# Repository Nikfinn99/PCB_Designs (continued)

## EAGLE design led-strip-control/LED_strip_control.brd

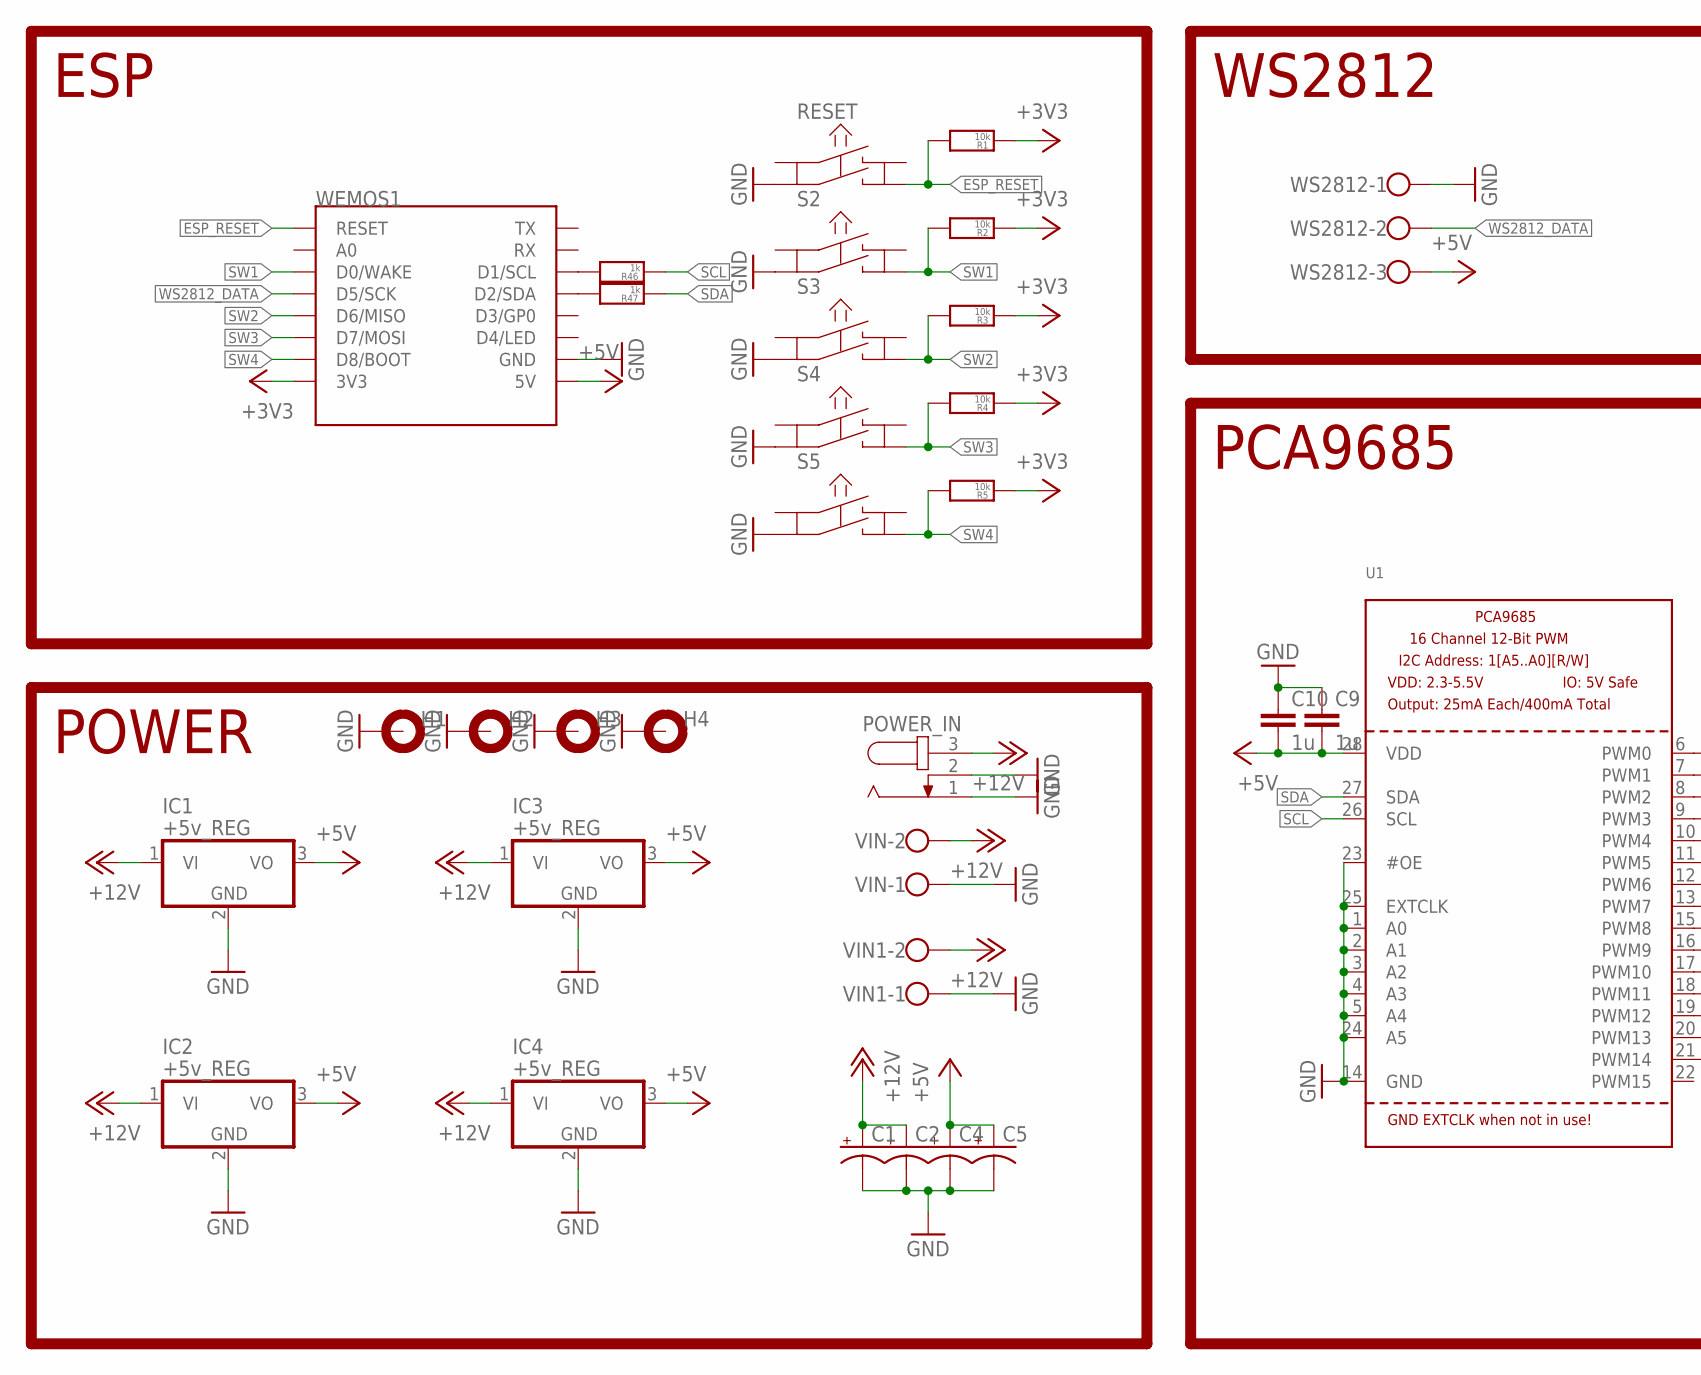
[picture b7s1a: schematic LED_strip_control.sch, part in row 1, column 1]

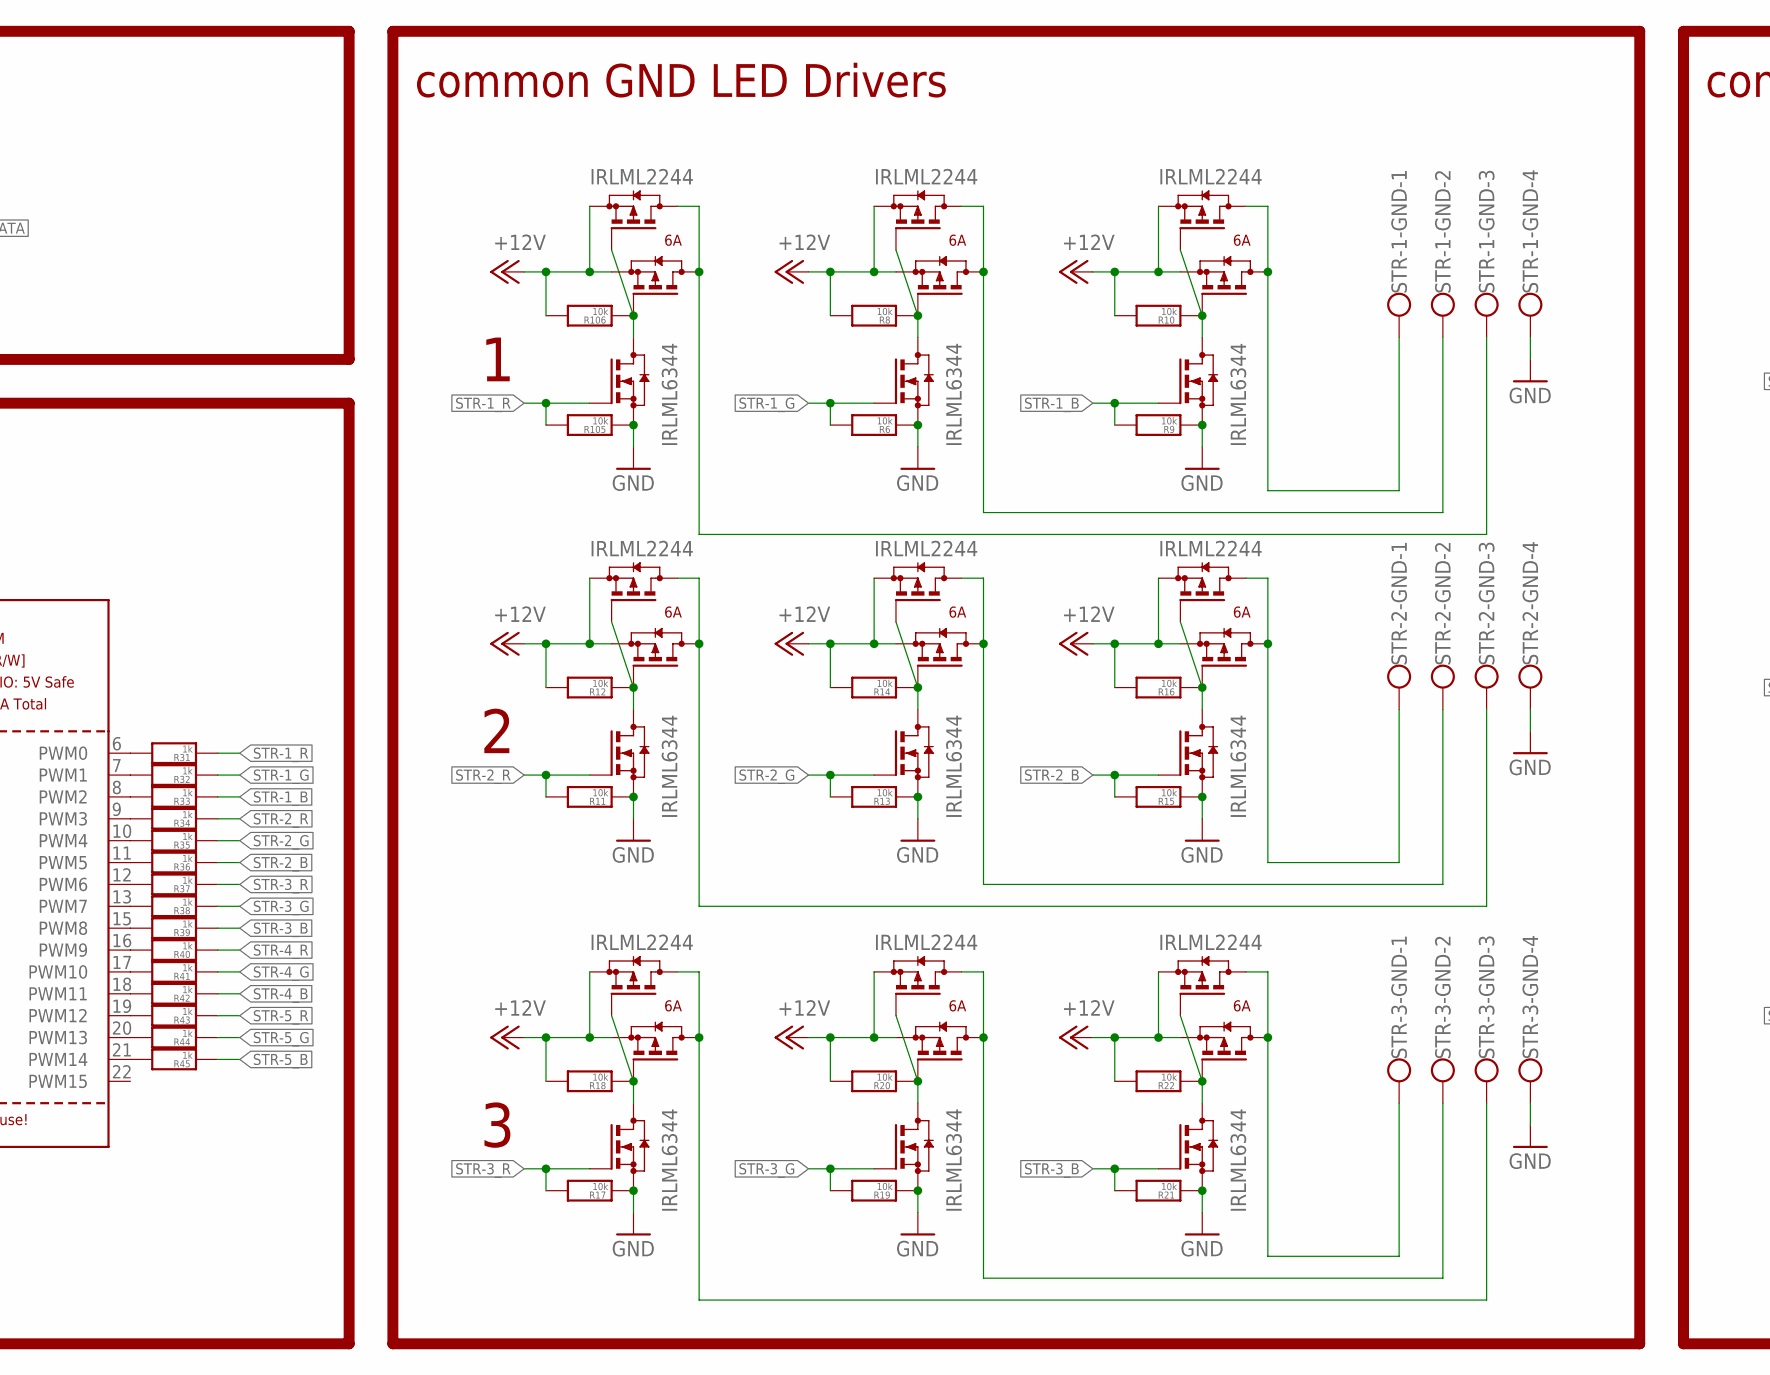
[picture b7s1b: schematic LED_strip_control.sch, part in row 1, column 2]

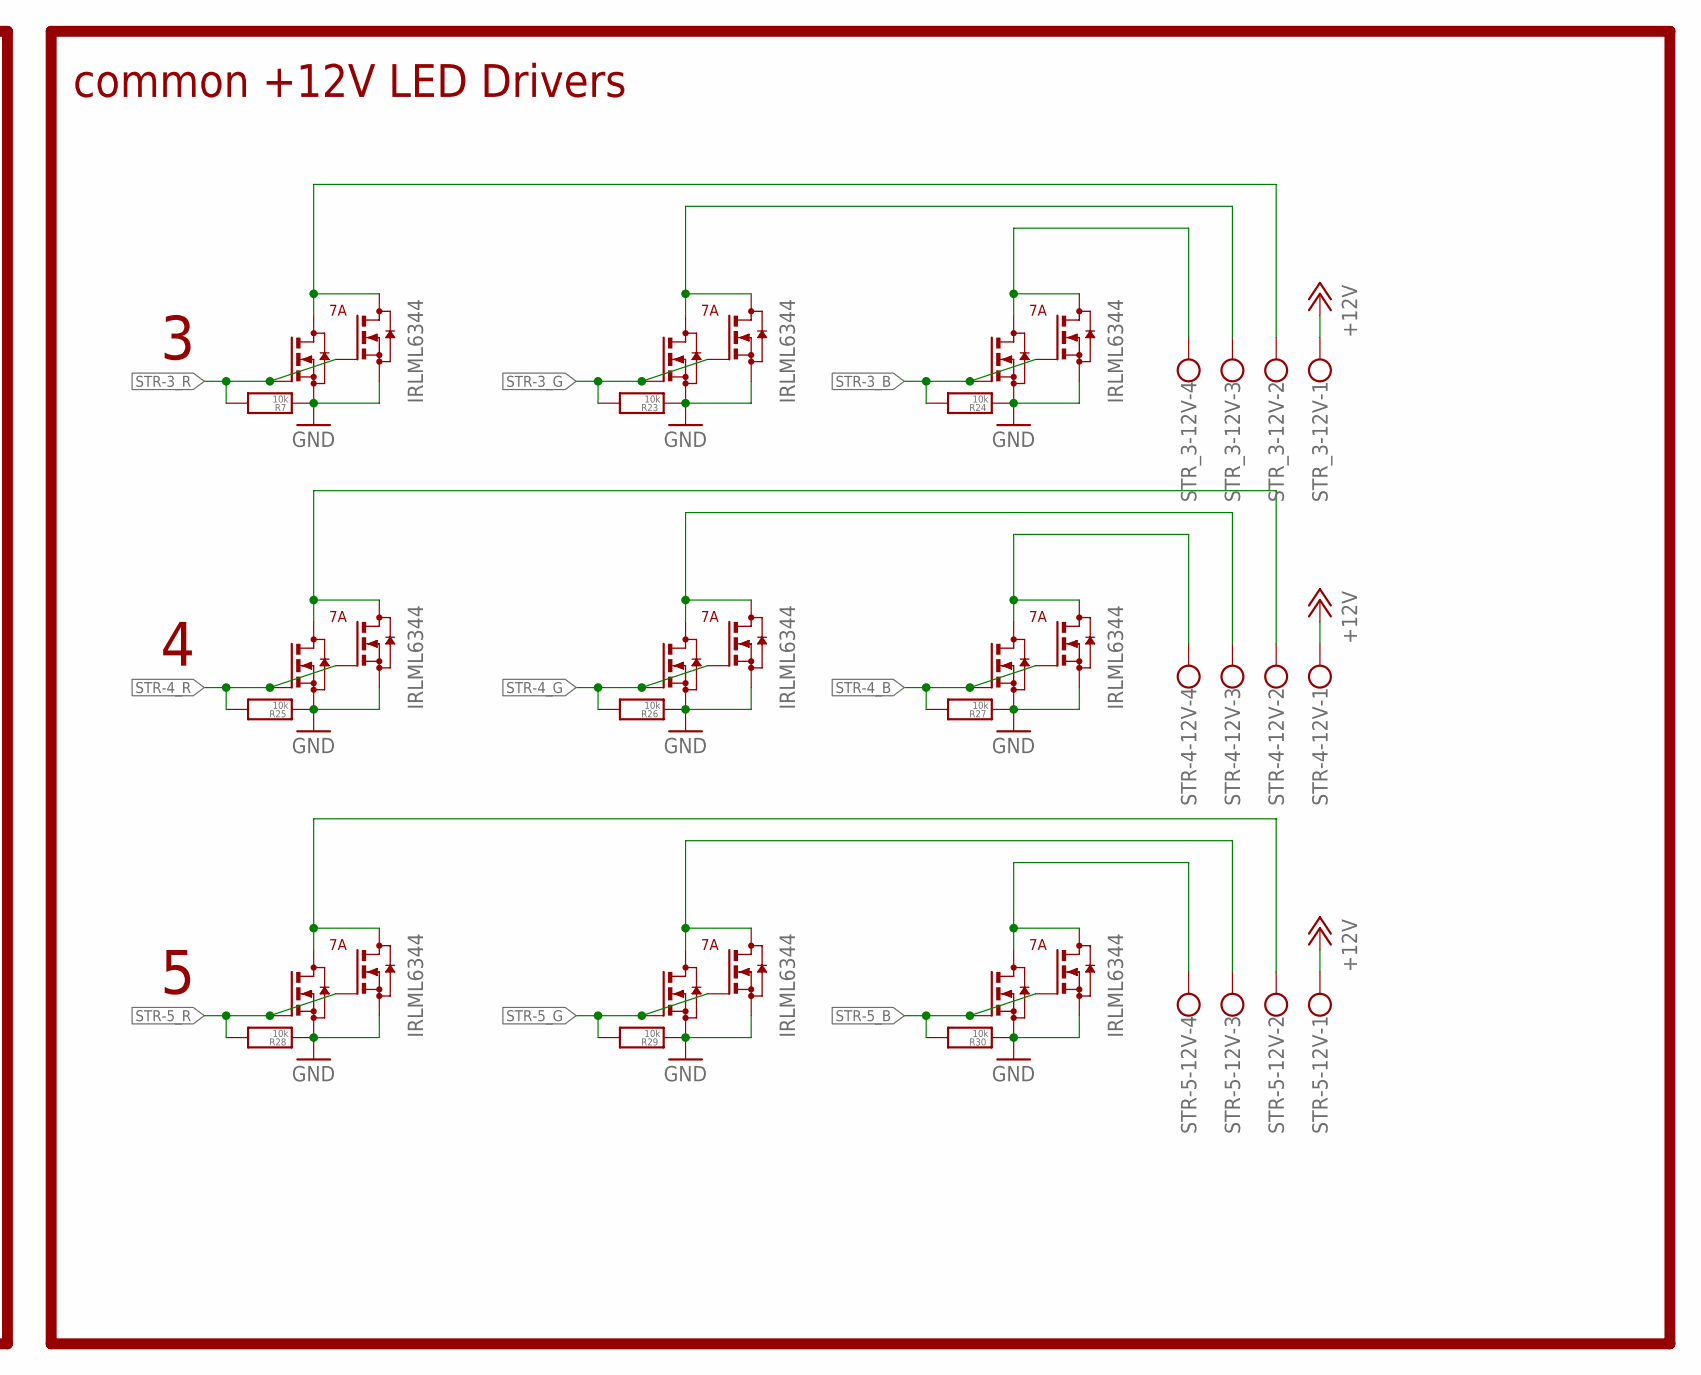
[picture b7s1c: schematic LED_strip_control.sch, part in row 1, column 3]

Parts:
C1, C2, C4, C5: CPOL-USE5-10.5; E5-10,5@1
C9, C10: 1u; C0805
H1, H2, H3, H4: MOUNT-PAD-ROUND3.2; 3,2-PAD
IC1, IC2, IC3, IC4: +5v_REG; TO220V
POWER_IN: RAPC7120; RAPC712
Q1, Q2, Q7, Q8, Q10, Q11, Q13, Q14, Q16, Q17, Q19, Q20, Q22, Q23, Q25, Q26, Q28, Q29: IRLML2244; SOT23
Q3, Q4, Q5, Q6, Q9, Q12, Q15, Q18, Q21, Q24, Q27, Q30, Q31, Q32, Q33, Q34, Q35, Q36, Q37, Q38, Q39, Q40, Q41, Q42, Q43, Q44, Q45: IRLML6344; SOT23
R1, R2, R3, R4, R5, R6, R7, R8, R9, R10, R11, R12, R13, R14, R15, R16, R17, R18, R19, R20, R21, R22, R23, R24, R25, R26, R27, R28, R29, R30, R105, R106: 10k; R0805
R31, R32, R33, R34, R35, R36, R37, R38, R39, R40, R41, R42, R43, R44, R45, R46, R47: 1k; R0805
RESET: KSM611A
S2, S3, S4, S5: KSM611A
STR-1-GND, STR-2-GND, STR-3-GND, STR-4-12V, STR-5-12V: KLEMME_4-PIN
STR_3-12V: KLEMME_4-PIN
U1: PCA9685; TSSOP28
VIN, VIN1: W237-102
WEMOS1: WEMOS-D1-MINI
WS2812: KLEMME_3-PIN

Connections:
+3V3: R1.1, R2.1, R3.1, R4.1, R5.1, WEMOS1.3V3
+5V: C4.+, C5.+, C9.2, C10.2, IC1.3 (VO), IC2.3 (VO), IC3.3 (VO), IC4.3 (VO), U1.28 (VDD), WEMOS1.5V, WS2812.3
+12V: C1.+, C2.+, IC1.1 (VI), IC2.1 (VI), IC3.1 (VI), IC4.1 (VI), POWER_IN.3, Q1.2 (S), Q2.2 (S), Q7.2 (S), Q8.2 (S), Q10.2 (S), Q11.2 (S), Q13.2 (S), Q14.2 (S), Q16.2 (S), Q17.2 (S), Q19.2 (S), Q20.2 (S), Q22.2 (S), Q23.2 (S), Q25.2 (S), Q26.2 (S), Q28.2 (S), Q29.2 (S), R8.2, R10.2, R12.2, R14.2, R16.2, R18.2, R20.2, R22.2, R106.2, STR-4-12V.1, STR-5-12V.1, STR_3-12V.1, VIN.2, VIN1.2
ESP_RESET: R1.2, RESET.D, WEMOS1.RESET
GND: C1.-, C2.-, C4.-, C5.-, C9.1, C10.1, H1.B3,2, H2.B3,2, H3.B3,2, H4.B3,2, IC1.2 (GND), IC2.2 (GND), IC3.2 (GND), IC4.2 (GND), POWER_IN.1, POWER_IN.2, Q3.2 (S), Q4.2 (S), Q5.2 (S), Q6.2 (S), Q9.2 (S), Q12.2 (S), Q15.2 (S), Q18.2 (S), Q21.2 (S), Q24.2 (S), Q27.2 (S), Q30.2 (S), Q31.2 (S), Q32.2 (S), Q33.2 (S), Q34.2 (S), Q35.2 (S), Q36.2 (S), Q37.2 (S), Q38.2 (S), Q39.2 (S), Q40.2 (S), Q41.2 (S), Q42.2 (S), Q43.2 (S), Q44.2 (S), Q45.2 (S), R6.1, R7.1, R9.1, R11.1, R13.1, R15.1, R17.1, R19.1, R21.1, R23.1, R24.1, R25.1, R26.1, R27.1, R28.1, R29.1, R30.1, R105.1, RESET.C, S2.C, S3.C, S4.C, S5.C, STR-1-GND.4, STR-2-GND.4, STR-3-GND.4, U1.1 (A0), U1.2 (A1), U1.3 (A2), U1.4 (A3), U1.5 (A4), U1.14 (GND), U1.23 (#OE), U1.24 (A5), U1.25 (EXTCLK), VIN.1, VIN1.1, WEMOS1.GND, WS2812.1
unnamed: Q12.3 (D), Q13.1 (G), Q14.1 (G), R12.1
unnamed: Q1.3 (D), Q2.3 (D), STR-1-GND.3
unnamed: Q6.3 (D), Q7.1 (G), Q8.1 (G), R8.1
unnamed: Q3.3 (D), Q5.3 (D), STR_3-12V.2
unnamed: Q34.3 (D), Q35.3 (D), STR-4-12V.2
unnamed: Q13.3 (D), Q14.3 (D), STR-2-GND.3
unnamed: Q7.3 (D), Q8.3 (D), STR-1-GND.2
unnamed: Q9.3 (D), Q10.1 (G), Q11.1 (G), R10.1
unnamed: Q15.3 (D), Q16.1 (G), Q17.1 (G), R14.1
unnamed: Q10.3 (D), Q11.3 (D), STR-1-GND.1
unnamed: Q16.3 (D), Q17.3 (D), STR-2-GND.2
unnamed: Q18.3 (D), Q19.1 (G), Q20.1 (G), R16.1
unnamed: Q19.3 (D), Q20.3 (D), STR-2-GND.1
unnamed: Q21.3 (D), Q22.1 (G), Q23.1 (G), R18.1
unnamed: Q22.3 (D), Q23.3 (D), STR-3-GND.3
unnamed: Q24.3 (D), Q25.1 (G), Q26.1 (G), R20.1
unnamed: Q25.3 (D), Q26.3 (D), STR-3-GND.2
unnamed: Q27.3 (D), Q28.1 (G), Q29.1 (G), R22.1
unnamed: Q28.3 (D), Q29.3 (D), STR-3-GND.1
unnamed: Q30.3 (D), Q31.3 (D), STR_3-12V.3
unnamed: Q36.3 (D), Q37.3 (D), STR-4-12V.3
unnamed: Q32.3 (D), Q33.3 (D), STR_3-12V.4
unnamed: Q38.3 (D), Q39.3 (D), STR-4-12V.4
unnamed: Q40.3 (D), Q41.3 (D), STR-5-12V.2
unnamed: Q42.3 (D), Q43.3 (D), STR-5-12V.3
unnamed: Q44.3 (D), Q45.3 (D), STR-5-12V.4
unnamed: R31.2, U1.6 (PWM0)
unnamed: R32.2, U1.7 (PWM1)
unnamed: R45.2, U1.21 (PWM14)
unnamed: R44.2, U1.20 (PWM13)
unnamed: R43.2, U1.19 (PWM12)
unnamed: R42.2, U1.18 (PWM11)
unnamed: R41.2, U1.17 (PWM10)
unnamed: R40.2, U1.16 (PWM9)
unnamed: R39.2, U1.15 (PWM8)
unnamed: R38.2, U1.13 (PWM7)
unnamed: R37.2, U1.12 (PWM6)
unnamed: R36.2, U1.11 (PWM5)
unnamed: R35.2, U1.10 (PWM4)
unnamed: R34.2, U1.9 (PWM3)
unnamed: R33.2, U1.8 (PWM2)
unnamed: R46.2, WEMOS1.D1 (D1/SCL)
unnamed: R47.2, WEMOS1.D2 (D2/SDA)
unnamed: Q1.1 (G), Q2.1 (G), Q4.3 (D), R106.1
SCL: R46.1, U1.26 (SCL)
SDA: R47.1, U1.27 (SDA)
STR-1_B: Q9.1 (G), R9.2, R33.1
STR-1_G: Q6.1 (G), R6.2, R32.1
STR-1_R: Q4.1 (G), R31.1, R105.2
STR-2_B: Q18.1 (G), R15.2, R36.1
STR-2_G: Q15.1 (G), R13.2, R35.1
STR-2_R: Q12.1 (G), R11.2, R34.1
STR-3_B: Q27.1 (G), Q32.1 (G), Q33.1 (G), R21.2, R24.2, R39.1
STR-3_G: Q24.1 (G), Q30.1 (G), Q31.1 (G), R19.2, R23.2, R38.1
STR-3_R: Q3.1 (G), Q5.1 (G), Q21.1 (G), R7.2, R17.2, R37.1
STR-4_B: Q38.1 (G), Q39.1 (G), R27.2, R42.1
STR-4_G: Q36.1 (G), Q37.1 (G), R26.2, R41.1
STR-4_R: Q34.1 (G), Q35.1 (G), R25.2, R40.1
STR-5_B: Q44.1 (G), Q45.1 (G), R30.2, R45.1
STR-5_G: Q42.1 (G), Q43.1 (G), R29.2, R44.1
STR-5_R: Q40.1 (G), Q41.1 (G), R28.2, R43.1
SW1: R2.2, S2.D, WEMOS1.D0 (D0/WAKE)
SW2: R3.2, S3.D, WEMOS1.D6 (D6/MISO)
SW3: R4.2, S4.D, WEMOS1.D7 (D7/MOSI)
SW4: R5.2, S5.D, WEMOS1.D8 (D8/BOOT)
WS2812_DATA: WEMOS1.D5 (D5/SCK), WS2812.2

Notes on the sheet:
ESP
POWER
WS2812
PCA9685
common GND LED Drivers
common +12V LED Drivers

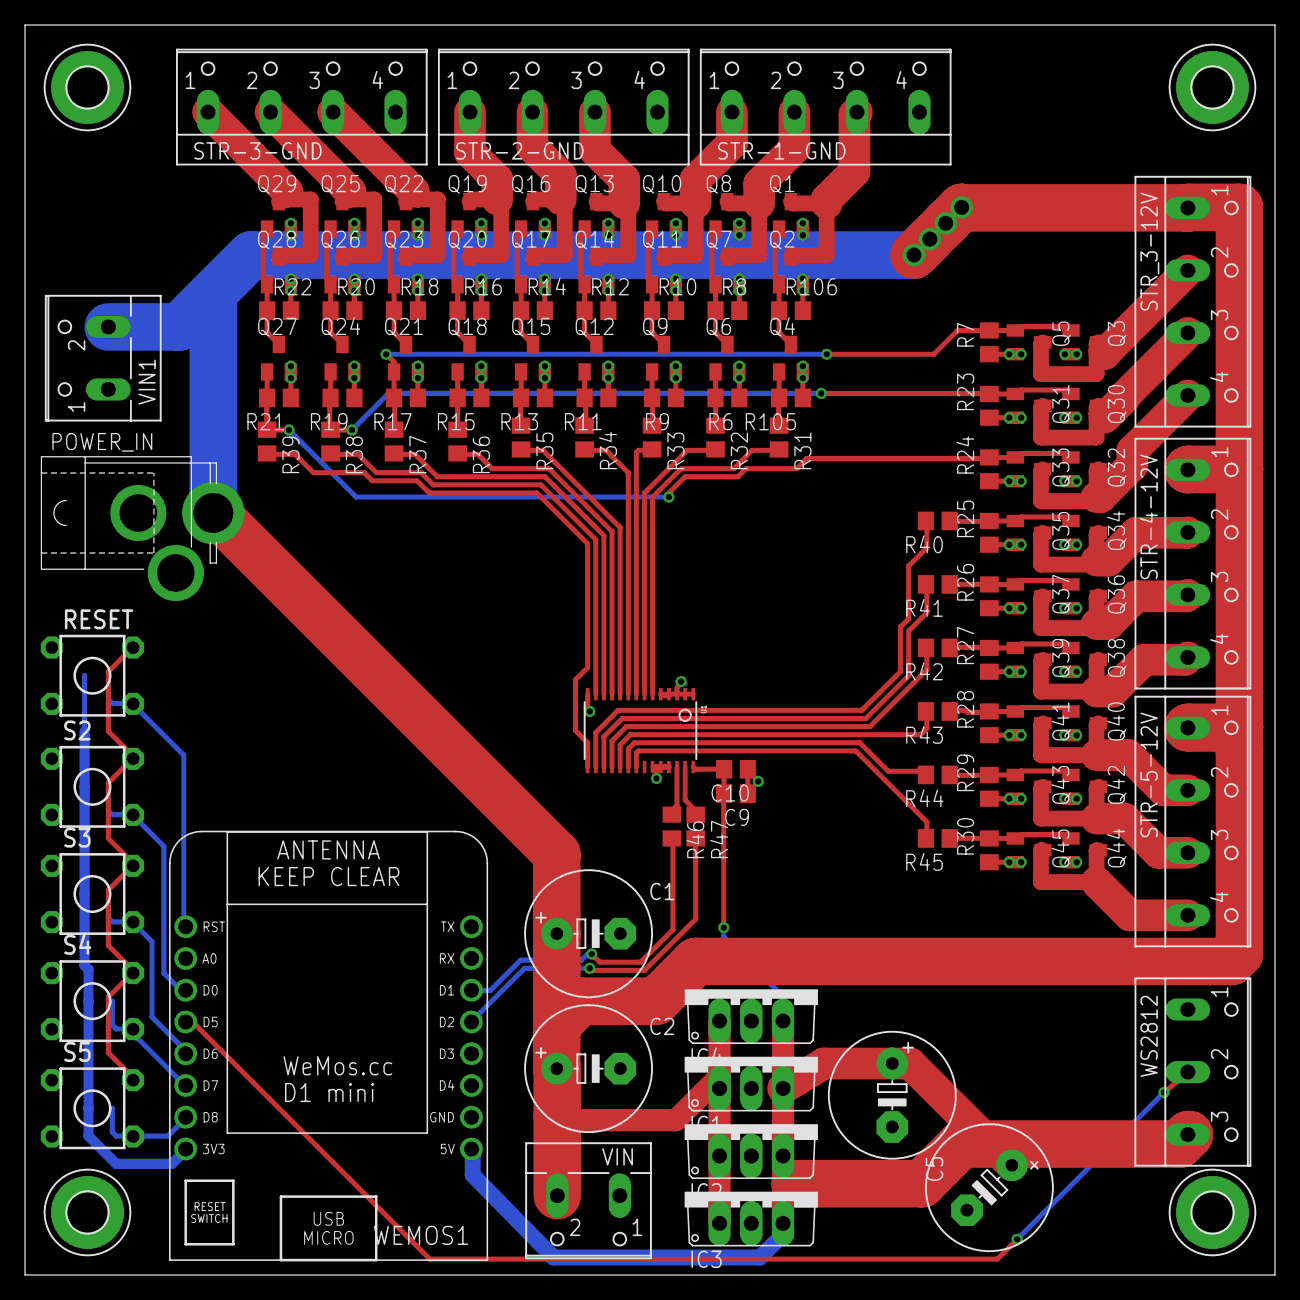
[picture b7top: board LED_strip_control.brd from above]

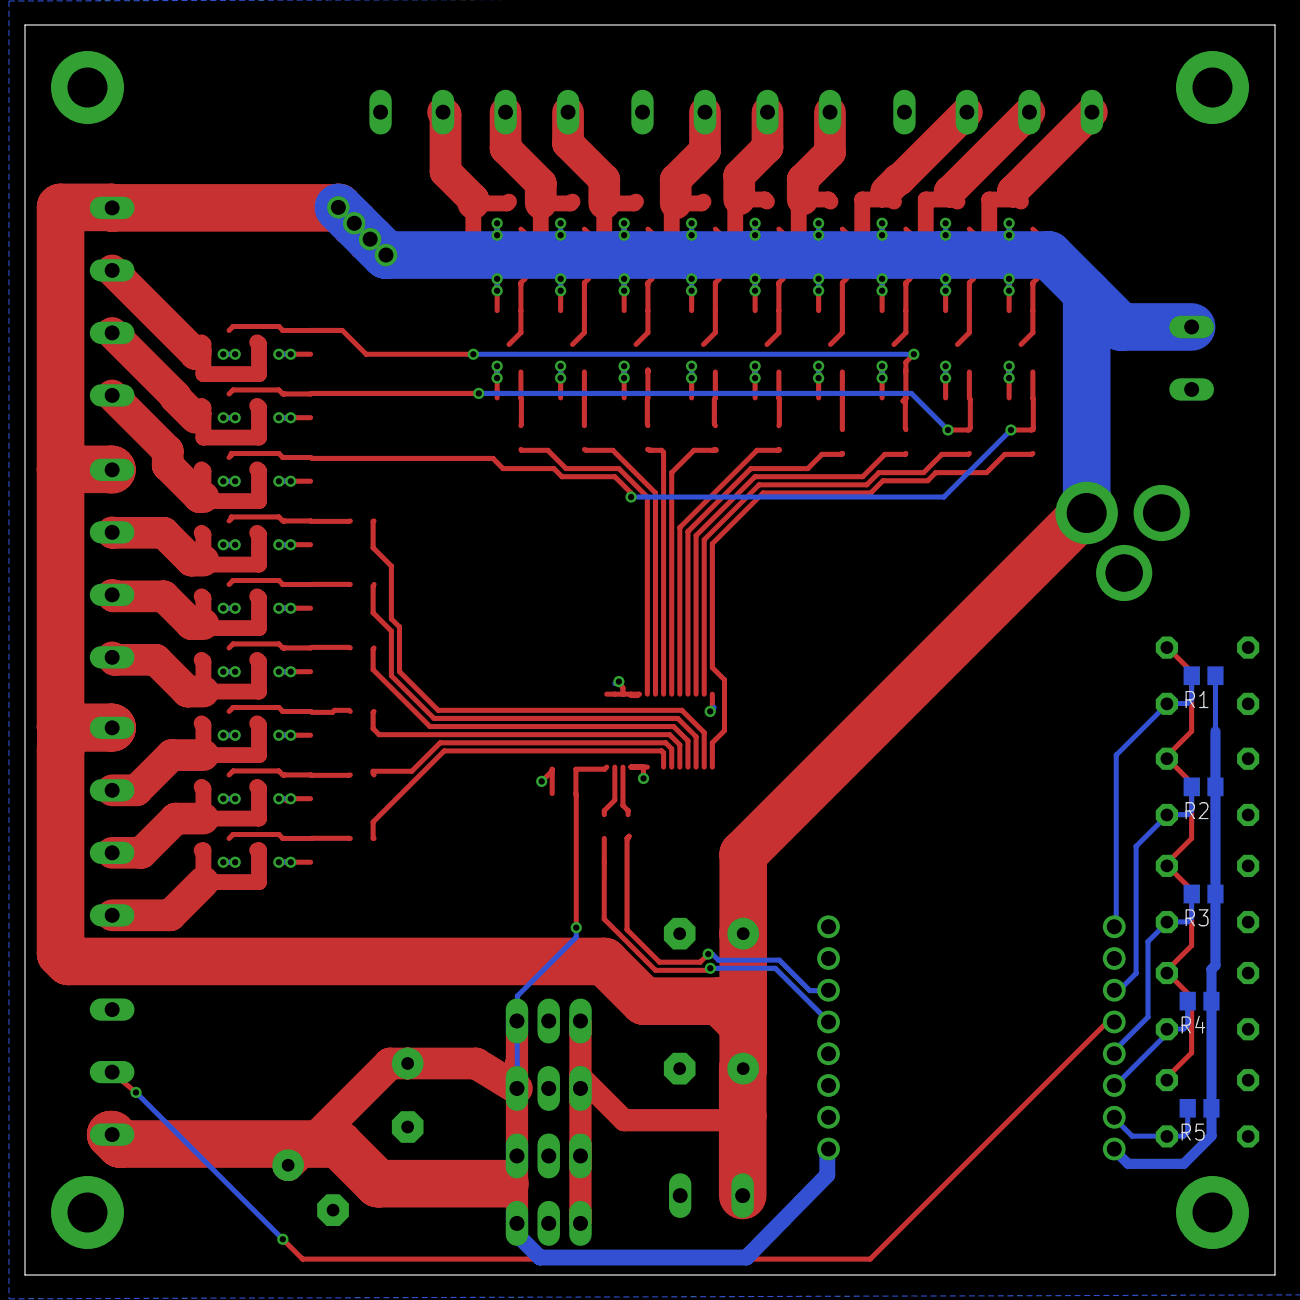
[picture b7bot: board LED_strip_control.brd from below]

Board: 2 copper layers, 100.0 x 100.0 mm, 125 parts (5 on the bottom side), 71 nets.

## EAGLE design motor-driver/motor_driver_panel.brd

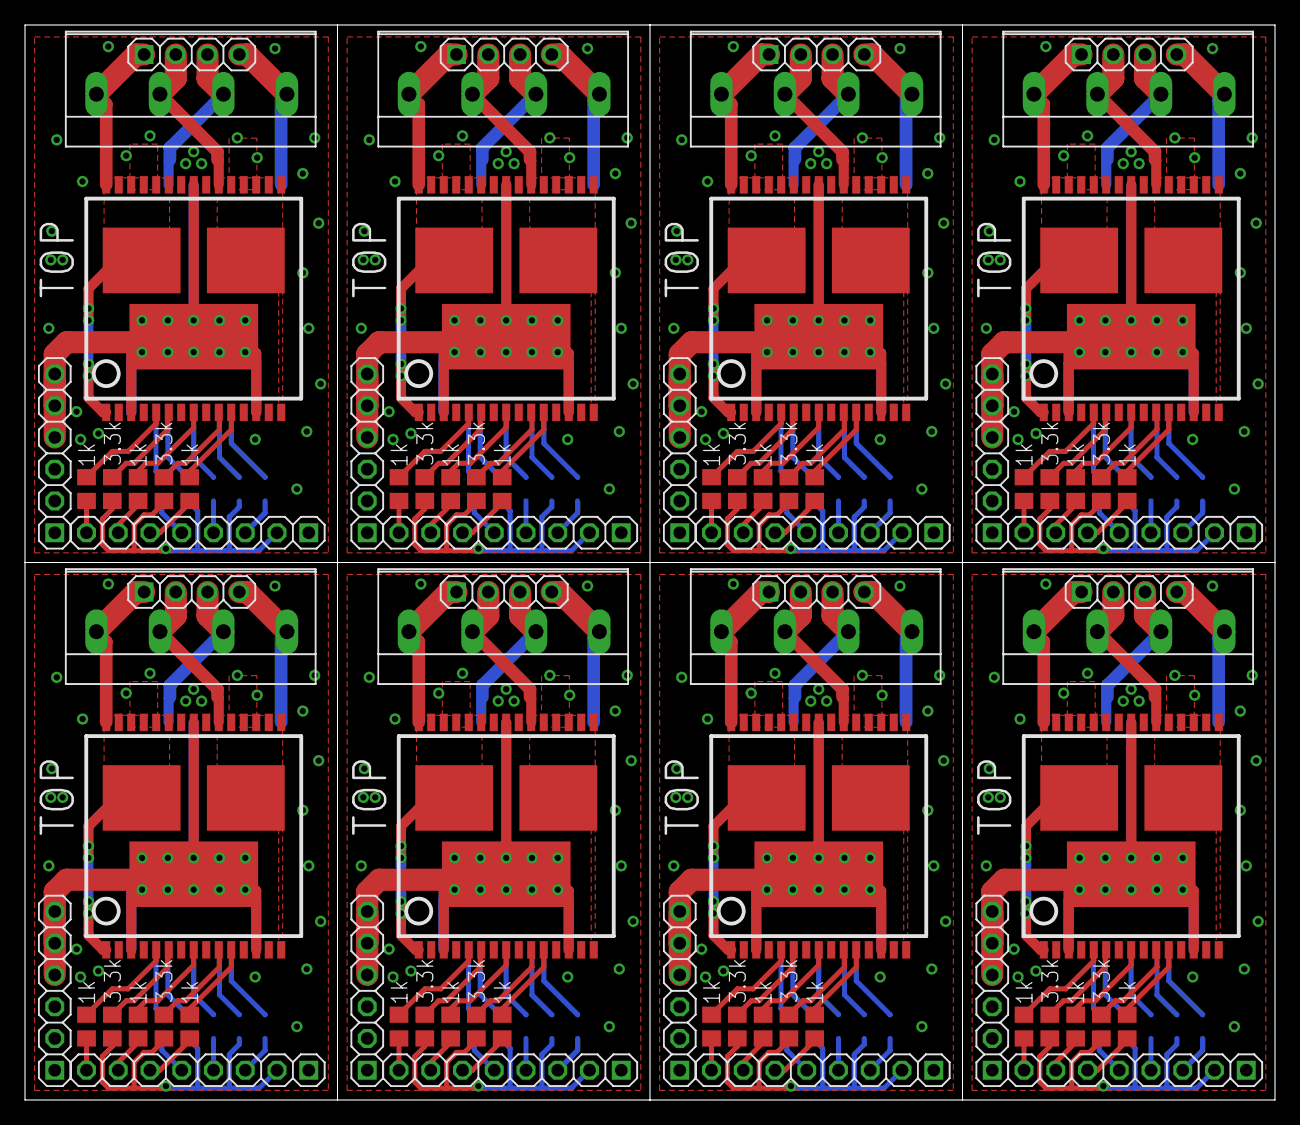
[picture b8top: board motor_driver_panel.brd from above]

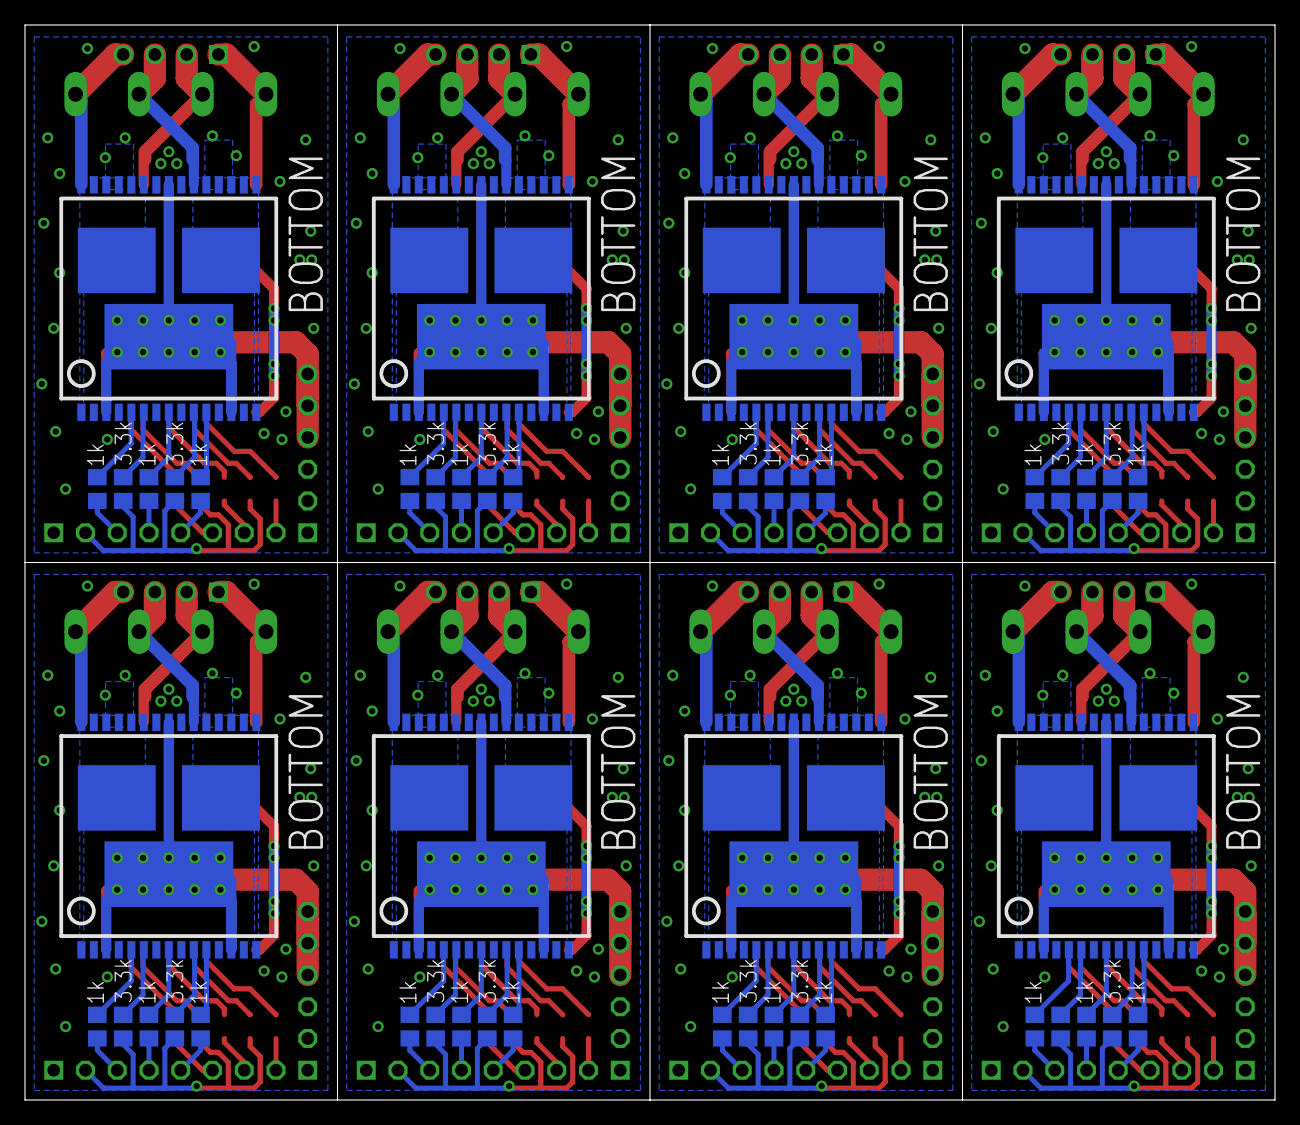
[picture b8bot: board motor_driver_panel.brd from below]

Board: 2 copper layers, 100.0 x 86.0 mm, 128 parts (48 on the bottom side), 184 nets.

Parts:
IC1, IC2, IC3, IC4, IC5, IC6, IC7, IC8, IC9, IC10, IC11, IC12, IC13, IC14, IC15, IC16: VNH2SP30-E; MP-SO-30
JP1, JP4, JP7, JP10, JP13, JP16, JP19, JP22: 1X08-S
JP2, JP5, JP8, JP11, JP14, JP17, JP20, JP23: 1X06-S
JP3, JP6, JP9, JP12, JP15, JP18, JP21, JP24: 1X04-S
R1, R2, R3, R4, R5, R10, R16, R17, R21, R22, R26, R27, R31, R32, R36, R37, R41, R42, R46, R47, R51, R52, R56, R57, R61, R62, R66, R67, R71, R72, R76, R77: 3.3k; R0805
R6, R7, R8, R9, R11, R12, R13, R14, R15, R18, R19, R20, R23, R24, R25, R28, R29, R30, R33, R34, R35, R38, R39, R40, R43, R44, R45, R48, R49, R50, R53, R54, R55, R58, R59, R60, R63, R64, R65, R68, R69, R70, R73, R74, R75, R78, R79, R80: 1k; R0805
X1, X2, X3, X4, X5, X6, X7, X8: KLEMME_4-PIN

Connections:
+5V: JP1.2, R3.2, R4.2, R5.2, R10.2
+5V1: JP4.2, R1.2, R2.2, R16.2, R17.2
+5V2: JP7.2, R21.2, R22.2, R26.2, R27.2
+5V3: JP10.2, R31.2, R32.2, R36.2, R37.2
+5V4: JP13.2, R41.2, R42.2, R46.2, R47.2
+5V5: JP16.2, R51.2, R52.2, R56.2, R57.2
+5V6: JP19.2, R61.2, R62.2, R66.2, R67.2
+5V7: JP22.2, R71.2, R72.2, R76.2, R77.2
+12V: IC1.P3, IC1.P13, IC1.P23, IC1.S1, IC2.P3, IC2.P13, IC2.P23, IC2.S1, JP2.4, JP2.5, JP2.6
+12V1: IC3.P3, IC3.P13, IC3.P23, IC3.S1, IC4.P3, IC4.P13, IC4.P23, IC4.S1, JP5.4, JP5.5, JP5.6
+12V2: IC5.P3, IC5.P13, IC5.P23, IC5.S1, IC6.P3, IC6.P13, IC6.P23, IC6.S1, JP8.4, JP8.5, JP8.6
+12V3: IC7.P3, IC7.P13, IC7.P23, IC7.S1, IC8.P3, IC8.P13, IC8.P23, IC8.S1, JP11.4, JP11.5, JP11.6
+12V4: IC9.P3, IC9.P13, IC9.P23, IC9.S1, IC10.P3, IC10.P13, IC10.P23, IC10.S1, JP14.4, JP14.5, JP14.6
+12V5: IC11.P3, IC11.P13, IC11.P23, IC11.S1, IC12.P3, IC12.P13, IC12.P23, IC12.S1, JP17.4, JP17.5, JP17.6
+12V6: IC13.P3, IC13.P13, IC13.P23, IC13.S1, IC14.P3, IC14.P13, IC14.P23, IC14.S1, JP20.4, JP20.5, JP20.6
+12V7: IC15.P3, IC15.P13, IC15.P23, IC15.S1, IC16.P3, IC16.P13, IC16.P23, IC16.S1, JP23.4, JP23.5, JP23.6
GND: IC1.P18, IC1.P19, IC1.P20, IC1.P26, IC1.P27, IC1.P28, IC2.P18, IC2.P19, IC2.P20, IC2.P26, IC2.P27, IC2.P28, JP1.1, JP2.1, JP2.2, JP2.3
GND1: IC3.P18, IC3.P19, IC3.P20, IC3.P26, IC3.P27, IC3.P28, IC4.P18, IC4.P19, IC4.P20, IC4.P26, IC4.P27, IC4.P28, JP4.1, JP5.1, JP5.2, JP5.3
GND2: IC5.P18, IC5.P19, IC5.P20, IC5.P26, IC5.P27, IC5.P28, IC6.P18, IC6.P19, IC6.P20, IC6.P26, IC6.P27, IC6.P28, JP7.1, JP8.1, JP8.2, JP8.3
GND3: IC7.P18, IC7.P19, IC7.P20, IC7.P26, IC7.P27, IC7.P28, IC8.P18, IC8.P19, IC8.P20, IC8.P26, IC8.P27, IC8.P28, JP10.1, JP11.1, JP11.2, JP11.3
GND4: IC9.P18, IC9.P19, IC9.P20, IC9.P26, IC9.P27, IC9.P28, IC10.P18, IC10.P19, IC10.P20, IC10.P26, IC10.P27, IC10.P28, JP13.1, JP14.1, JP14.2, JP14.3
GND5: IC11.P18, IC11.P19, IC11.P20, IC11.P26, IC11.P27, IC11.P28, IC12.P18, IC12.P19, IC12.P20, IC12.P26, IC12.P27, IC12.P28, JP16.1, JP17.1, JP17.2, JP17.3
GND6: IC13.P18, IC13.P19, IC13.P20, IC13.P26, IC13.P27, IC13.P28, IC14.P18, IC14.P19, IC14.P20, IC14.P26, IC14.P27, IC14.P28, JP19.1, JP20.1, JP20.2, JP20.3
GND7: IC15.P18, IC15.P19, IC15.P20, IC15.P26, IC15.P27, IC15.P28, IC16.P18, IC16.P19, IC16.P20, IC16.P26, IC16.P27, IC16.P28, JP22.1, JP23.1, JP23.2, JP23.3
M1_FW: JP1.8, R11.2
M1_FW1: JP4.8, R9.2
M1_FW2: JP7.8, R23.2
M1_FW3: JP10.8, R33.2
M1_FW4: JP13.8, R43.2
M1_FW5: JP16.8, R53.2
M1_FW6: JP19.8, R63.2
M1_FW7: JP22.8, R73.2
M1_PWM: JP1.7, R12.2
M1_PWM1: JP4.7, R14.2
M1_PWM2: JP7.7, R24.2
M1_PWM3: JP10.7, R34.2
M1_PWM4: JP13.7, R44.2
M1_PWM5: JP16.7, R54.2
M1_PWM6: JP19.7, R64.2
M1_PWM7: JP22.7, R74.2
M1_RW: JP1.6, R13.1
M1_RW1: JP4.6, R15.1
M1_RW2: JP7.6, R25.1
M1_RW3: JP10.6, R35.1
M1_RW4: JP13.6, R45.1
M1_RW5: JP16.6, R55.1
M1_RW6: JP19.6, R65.1
M1_RW7: JP22.6, R75.1
M2_FW: JP1.3, R6.2
M2_FW1: JP4.3, R18.2
M2_FW2: JP7.3, R28.2
M2_FW3: JP10.3, R38.2
M2_FW4: JP13.3, R48.2
M2_FW5: JP16.3, R58.2
M2_FW6: JP19.3, R68.2
M2_FW7: JP22.3, R78.2
M2_PWM: JP1.4, R7.2
M2_PWM1: JP4.4, R19.2
M2_PWM2: JP7.4, R29.2
M2_PWM3: JP10.4, R39.2
M2_PWM4: JP13.4, R49.2
M2_PWM5: JP16.4, R59.2
M2_PWM6: JP19.4, R69.2
M2_PWM7: JP22.4, R79.2
M2_RW: JP1.5, R8.1
M2_RW1: JP4.5, R20.1
M2_RW2: JP7.5, R30.1
M2_RW3: JP10.5, R40.1
M2_RW4: JP13.5, R50.1
M2_RW5: JP16.5, R60.1
M2_RW6: JP19.5, R70.1
M2_RW7: JP22.5, R80.1
unnamed: IC2.P5, R6.1
unnamed: IC2.P6, R5.1
unnamed: IC1.P5, R11.1
unnamed: IC2.P10, R3.1
unnamed: IC3.P5, R9.1
unnamed: IC2.P8, R7.1
unnamed: IC1.P6, R10.1
unnamed: IC1.P10, R4.1
unnamed: IC3.P6, R2.1
unnamed: IC1.P8, R12.1
unnamed: IC1.P11, R13.2
unnamed: IC1.P1, IC1.P25, IC1.P30, IC1.S2, JP3.1, X1.1
unnamed: IC1.P15, IC1.P16, IC1.P21, IC1.S3, JP3.2, X1.2
unnamed: IC2.P11, R8.2
unnamed: IC3.P10, R1.1
unnamed: IC3.P8, R14.1
unnamed: IC2.P15, IC2.P16, IC2.P21, IC2.S3, JP3.3, X1.3
unnamed: IC3.P11, R15.2
unnamed: IC2.P1, IC2.P25, IC2.P30, IC2.S2, JP3.4, X1.4
unnamed: IC3.P1, IC3.P25, IC3.P30, IC3.S2, JP6.1, X2.1
unnamed: IC3.P15, IC3.P16, IC3.P21, IC3.S3, JP6.2, X2.2
unnamed: IC4.P5, R18.1
unnamed: IC4.P6, R17.1
unnamed: IC4.P10, R16.1
unnamed: IC4.P8, R19.1
unnamed: IC4.P11, R20.2
unnamed: IC4.P15, IC4.P16, IC4.P21, IC4.S3, JP6.3, X2.3
unnamed: IC4.P1, IC4.P25, IC4.P30, IC4.S2, JP6.4, X2.4
unnamed: IC5.P5, R23.1
unnamed: IC5.P6, R22.1
unnamed: IC5.P10, R21.1
unnamed: IC5.P8, R24.1
unnamed: IC5.P11, R25.2
unnamed: IC5.P1, IC5.P25, IC5.P30, IC5.S2, JP9.1, X3.1
unnamed: IC5.P15, IC5.P16, IC5.P21, IC5.S3, JP9.2, X3.2
unnamed: IC6.P5, R28.1
unnamed: IC6.P6, R27.1
unnamed: IC6.P10, R26.1
unnamed: IC6.P8, R29.1
unnamed: IC6.P11, R30.2
unnamed: IC6.P15, IC6.P16, IC6.P21, IC6.S3, JP9.3, X3.3
unnamed: IC6.P1, IC6.P25, IC6.P30, IC6.S2, JP9.4, X3.4
unnamed: IC7.P5, R33.1
unnamed: IC7.P6, R32.1
unnamed: IC7.P10, R31.1
unnamed: IC7.P8, R34.1
unnamed: IC7.P11, R35.2
unnamed: IC7.P1, IC7.P25, IC7.P30, IC7.S2, JP12.1, X4.1
unnamed: IC7.P15, IC7.P16, IC7.P21, IC7.S3, JP12.2, X4.2
unnamed: IC8.P5, R38.1
unnamed: IC8.P6, R37.1
unnamed: IC8.P10, R36.1
unnamed: IC8.P8, R39.1
unnamed: IC8.P11, R40.2
unnamed: IC8.P15, IC8.P16, IC8.P21, IC8.S3, JP12.3, X4.3
unnamed: IC8.P1, IC8.P25, IC8.P30, IC8.S2, JP12.4, X4.4
unnamed: IC9.P5, R43.1
unnamed: IC9.P6, R42.1
unnamed: IC9.P10, R41.1
unnamed: IC9.P8, R44.1
unnamed: IC9.P11, R45.2
unnamed: IC9.P1, IC9.P25, IC9.P30, IC9.S2, JP15.1, X5.1
unnamed: IC9.P15, IC9.P16, IC9.P21, IC9.S3, JP15.2, X5.2
unnamed: IC10.P5, R48.1
unnamed: IC10.P6, R47.1
unnamed: IC10.P10, R46.1
unnamed: IC10.P8, R49.1
unnamed: IC10.P11, R50.2
unnamed: IC10.P15, IC10.P16, IC10.P21, IC10.S3, JP15.3, X5.3
unnamed: IC10.P1, IC10.P25, IC10.P30, IC10.S2, JP15.4, X5.4
unnamed: IC11.P5, R53.1
unnamed: IC11.P6, R52.1
unnamed: IC11.P10, R51.1
unnamed: IC11.P8, R54.1
unnamed: IC11.P11, R55.2
unnamed: IC11.P1, IC11.P25, IC11.P30, IC11.S2, JP18.1, X6.1
unnamed: IC11.P15, IC11.P16, IC11.P21, IC11.S3, JP18.2, X6.2
unnamed: IC12.P5, R58.1
unnamed: IC12.P6, R57.1
unnamed: IC12.P10, R56.1
unnamed: IC12.P8, R59.1
unnamed: IC12.P11, R60.2
unnamed: IC12.P15, IC12.P16, IC12.P21, IC12.S3, JP18.3, X6.3
unnamed: IC12.P1, IC12.P25, IC12.P30, IC12.S2, JP18.4, X6.4
unnamed: IC13.P5, R63.1
unnamed: IC13.P6, R62.1
unnamed: IC13.P10, R61.1
unnamed: IC13.P8, R64.1
unnamed: IC13.P11, R65.2
unnamed: IC13.P1, IC13.P25, IC13.P30, IC13.S2, JP21.1, X7.1
unnamed: IC13.P15, IC13.P16, IC13.P21, IC13.S3, JP21.2, X7.2
unnamed: IC14.P5, R68.1
unnamed: IC14.P6, R67.1
unnamed: IC14.P10, R66.1
unnamed: IC14.P8, R69.1
unnamed: IC14.P11, R70.2
unnamed: IC14.P15, IC14.P16, IC14.P21, IC14.S3, JP21.3, X7.3
unnamed: IC14.P1, IC14.P25, IC14.P30, IC14.S2, JP21.4, X7.4
unnamed: IC15.P5, R73.1
unnamed: IC15.P6, R72.1
unnamed: IC15.P10, R71.1
unnamed: IC15.P8, R74.1
unnamed: IC15.P11, R75.2
unnamed: IC15.P1, IC15.P25, IC15.P30, IC15.S2, JP24.1, X8.1
unnamed: IC15.P15, IC15.P16, IC15.P21, IC15.S3, JP24.2, X8.2
unnamed: IC16.P5, R78.1
unnamed: IC16.P6, R77.1
unnamed: IC16.P10, R76.1
unnamed: IC16.P8, R79.1
unnamed: IC16.P11, R80.2
unnamed: IC16.P15, IC16.P16, IC16.P21, IC16.S3, JP24.3, X8.3
unnamed: IC16.P1, IC16.P25, IC16.P30, IC16.S2, JP24.4, X8.4

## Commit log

2019-04-30 Create LICENSE
2019-08-25 update 7 channel pwm design
2019-08-25 update tap switch 7btn design
2019-08-25 add audio mixer pcb
2019-08-25 add image for motor driver
2019-08-25 add door sensor pcb
